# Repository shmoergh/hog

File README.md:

# Hog

Fully analog two-voice monophonic synth for live performances.

Details and user guide: [shmoergh.com](https://shmoergh.com/)

Latest revision: rev #3.

## Build

The HOG is a very fun but equally advanced electronics project. It's fully open source and we've put together a build guide for the brave ones who decide to build one. Let us know if you have questions and definitely share some pics of your builds (follow [Shmøergh on Instagram](https://www.instagram.com/shmoergh/)).

[Open build guide &rarr;](https://www.shmoergh.com/guides/hog-build-guide)

## BOMs

The HOG consists of 5 separate boards which you can find in the `boards` folder. Each board has it's own gerber files for JLCPCB PCB and Mouser BOMs in the board's `production` folders. The Core and Filter boards have SMD components too for which you can find JLCPCB assembly files (BOM and position) in the `production/jlcpcb` folder.

## Cloning

The MIDI2CV module uses [`pico-lib`](https://github.com/peterzimon/pico-lib) submodule. Make sure you clone
the repo like with its submodules:

```console
git clone --recurse-submodules git@github.com:shmoergh/hog.git
```

## License

Shmoergh Hog © 2024

Hardware is licensed under [CC BY-NC 4.0](https://creativecommons.org/licenses/by-nc/4.0/)

Software is licensed under [MIT](https://opensource.org/license/mit).

Font used on PCBs: <https://departuremono.com>

Simulations made in [CircuitJS](https://www.falstad.com/circuit/circuitjs.html)

## Disclaimer

All electronic projects and designs presented on this web site, or associated web sites should be considered dangerous if not lethal if not used safely. When working on projects based on the designs on this site, use extreme care to ensure that you do not come into contact with mains AC voltages or high voltage DC. If you are not confident about working with mains voltages, or high voltages, or you are not legally allowed to work with mains voltages, or high voltages, you are advised not to attempt work on them. The author, host, and all people associated with these web pages disclaim any liability for damages should anyone be killed or injured while working on these projects, or projects based on these designs, or any other project or design presented on these web pages and any associated web pages. The author, host, and all people associated with these web pages also disclaim any liability for projects, or projects based on these designs, or any other project or design presented on these web pages and any associated web pages when used in such a way as to infringe relevant government regulations and by-laws.

All circuits, schematics, printed circuit board, panel design and associated data published on this site can be used for private use only.

We are not responsible for any errors in the PCB design or the parts list. All responsibility for ordering PCBs, components, and assembly services rests solely with you.

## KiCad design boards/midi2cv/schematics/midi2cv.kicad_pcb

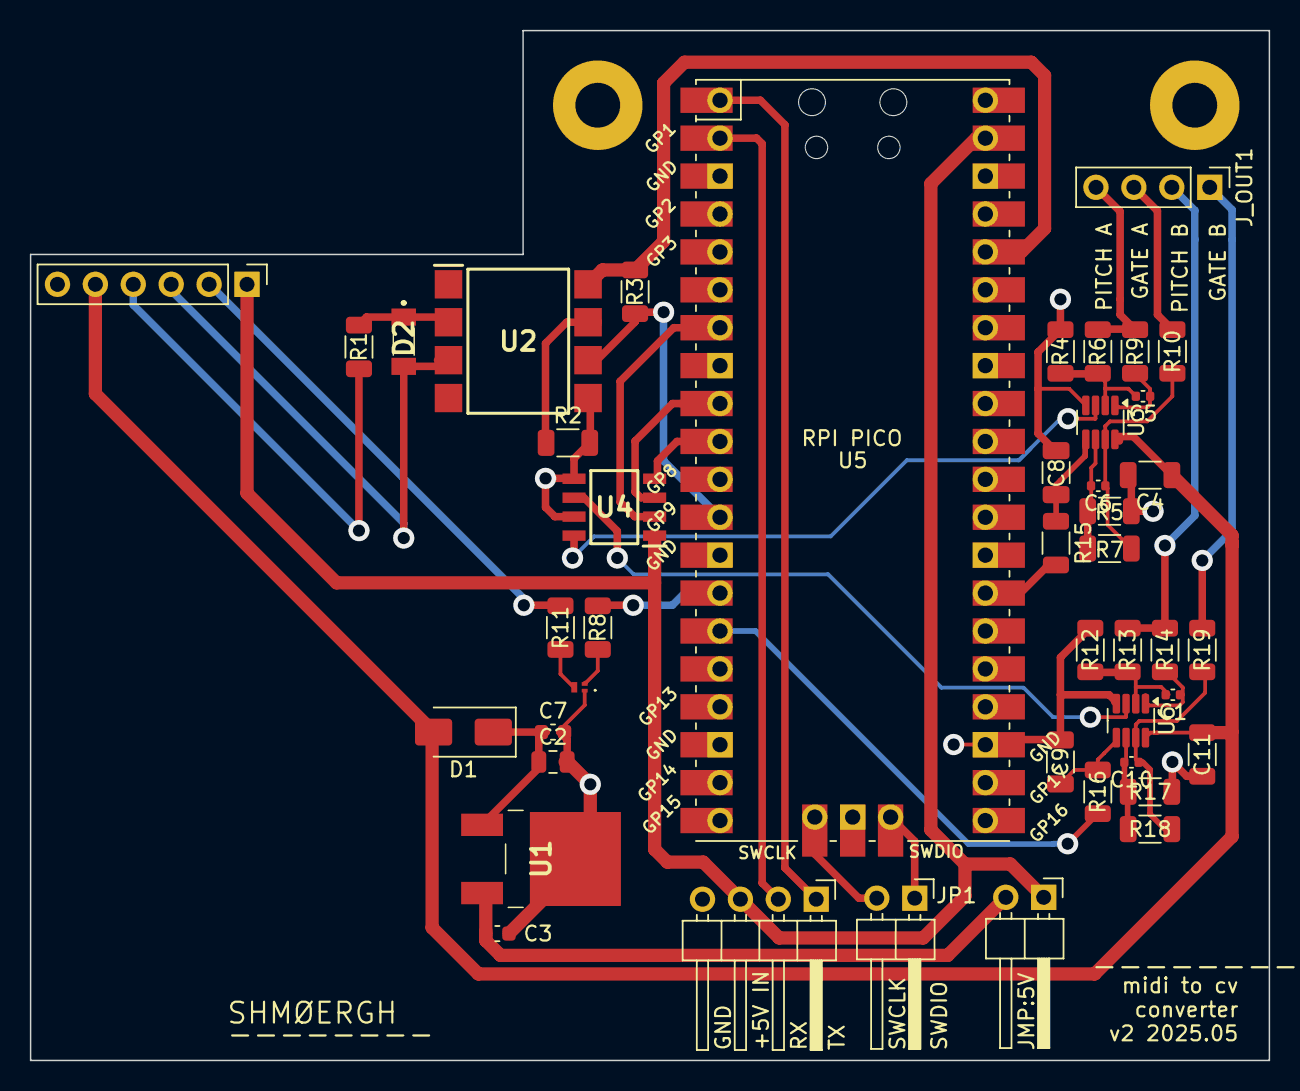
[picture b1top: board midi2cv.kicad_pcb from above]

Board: 2 copper layers, 83.0 x 69.0 mm, 46 parts (0 on the bottom side), 40 nets.

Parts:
C1, C5, C6, C10: 22p; C_0402_1005Metric
C2: 330n; C_0805_2012Metric
C3: 100n; C_0603_1608Metric
C4, C11: 100n; R_1206_3216Metric
C7: 10u; C_0603_1608Metric
C8, C9: 1u; C_1206_3216Metric
D1: S1A; D_SMA
D2: FDLL4148; FDLL4448
H1, H2: MountingHole; MountingHole_3mm_Pad
JP1: Jumper_2_Open; PinHeader_1x02_P2.54mm_Horizontal
J_IN1: Conn_01x06; PinHeader_1x06_P2.54mm_Vertical
J_OUT1: Conn_01x04; PinHeader_1x04_P2.54mm_Vertical
J_SWCLKDIO1: Conn_01x02; PinHeader_1x02_P2.54mm_Horizontal
J_SWD_IO1: Conn_01x04; PinHeader_1x04_P2.54mm_Horizontal
Q_GATE_LED1: MMBT3904LP-7; MMBT3904LP7
R1, R3: 220; R_1206_3216Metric
R2: 4.7k; R_1206_3216Metric
R4, R12: 47k; R_1206_3216Metric
R5, R17: 100k; R_1206_3216Metric
R6, R13: 68k; R_1206_3216Metric
R7, R18: 51k; R_1206_3216Metric
R8: 10k; R_1206_3216Metric
R9, R10, R14, R15, R16, R19: 1k; R_1206_3216Metric
R11: 470; R_1206_3216Metric
U1: L7805CDT-TR; L7805CDTTR
U2: 6N138S-TA1; SOP254P1030X508-8N
U3, U6: LM358; SOT-23-8
U4: MCP4822-E/SN; SOIC127P600X175-8N
U5: Pico; RPi_Pico_SMD_TH

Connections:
+3.3V: R3.1, U2.8 (VCC), U5.36 (3V3)
+5V: JP1.1 (A), J_IN1.1, J_SWD_IO1.3, U4.1 (Vdd), U5.39 (VSYS)
+12V: C4.1, C11.1, D1.2 (A), J_IN1.5, U3.8 (V+), U6.8 (V+)
DAC_A: U3.3 (+), U4.8 (VA)
DAC_B: U4.6 (VB), U6.3 (+)
DAC_CS: U4.2 (~CS), U5.7 (GPIO5)
DAC_SCK: U4.3 (SCK), U5.9 (GPIO6)
DAC_SDI: U4.4 (SDI), U5.10 (GPIO7)
GATE_A: J_OUT1.3, R10.1
GATE_A_TRIG: R15.2, U5.27 (GPIO21)
GATE_B: J_OUT1.1, R19.1
GATE_B_TRIG: R16.2, U5.15 (GPIO11)
GND: C2.2, C3.2, C4.2, C7.2, C8.2, C9.2, C11.2, J_IN1.6, J_SWD_IO1.4, Q_GATE_LED1.1 (E), R2.2, R4.2, R5.2, R12.2, R17.2, U1.2 (GND), U2.5 (GND), U3.4 (V-), U4.5 (~LDAC), U4.7 (Vss), U5.3 (GND), U5.8 (GND), U5.13 (GND), U5.18 (GND), U5.23 (GND), U5.28 (GND), U5.38 (GND), U6.4 (V-)
LED_GND: J_IN1.2, R11.1
LED_OUT: R8.1, U5.14 (GPIO10)
MIDI_4R: J_IN1.4, R1.2
MIDI_5T: D2.2 (A), J_IN1.3, U2.3 (C2)
MIDI_IN: R3.2, U2.6 (VO2), U5.12 (GPIO9)
unnamed: C1.1, R14.2, U6.1
unnamed: C5.1, R9.2, U3.1
unnamed: C6.1, R7.1, R10.2, U3.7
unnamed: C10.1, R18.1, R19.2, U6.7
unnamed: C2.1, C7.1, D1.1 (K), U1.1 (INPUT)
unnamed: D2.1 (K), R1.1, U2.2 (C1)
unnamed: C3.1, JP1.2 (B), U1.3 (OUTPUT)
unnamed: J_SWCLKDIO1.1, U5.43 (SWDIO)
unnamed: J_SWCLKDIO1.2, U5.41 (SWCLK)
unnamed: Q_GATE_LED1.2 (B), R8.2
unnamed: Q_GATE_LED1.3 (C), R11.2
unnamed: R2.1, U2.7 (VO1)
unnamed: C5.2, R4.1, R6.2, U3.2 (-)
unnamed: C8.1, R15.1, U3.5 (+)
unnamed: C6.2, R5.1, R7.2, U3.6 (-)
unnamed: C1.2, R12.1, R13.2, U6.2 (-)
unnamed: C9.1, R16.1, U6.5 (+)
unnamed: C10.2, R17.1, R18.2, U6.6 (-)
PITCH_A: J_OUT1.4, R6.1, R9.1
PITCH_B: J_OUT1.2, R13.1, R14.1
UART_RX: J_SWD_IO1.2, U5.2 (GPIO1)
UART_TX: J_SWD_IO1.1, U5.1 (GPIO0)

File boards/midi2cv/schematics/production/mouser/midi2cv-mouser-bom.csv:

"Reference","Value","Datasheet","Footprint","Quantity 1","DNP","Mouser Part Number","Part URL","Vendor"
"C1,C5,C6,C10","22p","~","-- mixed values --","4",,"594-K220J15C0GF53L2 ","https://mou.sr/3ZTXYXB","Mouser"
"C2","330n","~","Capacitor_THT:C_Disc_D3.0mm_W2.0mm_P2.50mm","1",,"810-FA14X7R1H334KNU6 ","https://mou.sr/4gDlMo9","Mouser"
"C3,C4,C11","100n","~","Capacitor_THT:C_Disc_D3.0mm_W2.0mm_P2.50mm","3",,"594-K103K15X7RF5TK2 ","https://mou.sr/3VFZIRH","Mouser"
"C7","10u","~","Capacitor_THT:CP_Radial_D6.3mm_P2.50mm","1",,"80-ESS106M035AC2EA ","https://mou.sr/49DyMaU","Mouser"
"C8,C9","1u","~","Capacitor_THT:CP_Radial_D6.3mm_P2.50mm","2",,"140-SG1R0M1H0407P ","https://mou.sr/41BqE8O","Mouser"
"D1","1N4001","~","Diode_THT:D_DO-41_SOD81_P10.16mm_Horizontal","1",,"637-1N4001 ","https://mou.sr/3DfEJyK","Mouser"
"D2","1N4148","~","Diode_THT:D_DO-35_SOD27_P7.62mm_Horizontal","1",,"512-1N4148 ","https://mou.sr/3ZP7Wt3","Mouser"
"JP1","Jumper_2_Open","~","Connector_PinHeader_2.54mm:PinHeader_1x02_P2.54mm_Horizontal","1",,"737-PH1RB-02-UA ","https://mou.sr/3D93YT9","Mouser"
"J_IN1","Conn_01x06","~","Connector_PinHeader_2.54mm:PinHeader_1x06_P2.54mm_Vertical","1",,"737-RS1-06-G ","https://mou.sr/3BuZUME","Mouser"
"J_OUT1,J_SWD_IO1","Conn_01x04","~","-- mixed values --","2",,"737-RS1-04-G ","https://mou.sr/4gDjs0p","Mouser"
"J_SWCLKDIO1","Conn_01x02","~","Connector_PinHeader_2.54mm:PinHeader_1x02_P2.54mm_Horizontal","1",,"737-PH1RB-02-UA ","https://mou.sr/3D93YT9","Mouser"
"Q_GATE_LED1","2N3904","https://www.onsemi.com/pub/Collateral/2N3903-D.PDF","Package_TO_SOT_THT:TO-92_Inline_Wide","1",,"637-2N3904 ","https://mou.sr/4febysZ","Mouser"
"R1,R3","220","~","Shmoergh_Custom_Footprints:R_Axial_DIN0207_L6.3mm_D2.5mm_P7.62mm_Horizontal","2",,"303-MF0W4FF2200B00 ","https://mou.sr/4iu83Sh","Mouser"
"R2","4.7k","~","Shmoergh_Custom_Footprints:R_Axial_DIN0207_L6.3mm_D2.5mm_P7.62mm_Horizontal","1",,"303-MF0W4FF4701A10 ","https://mou.sr/41yABnC","Mouser"
"R4,R12","47k","~","Shmoergh_Custom_Footprints:R_Axial_DIN0207_L6.3mm_D2.5mm_P7.62mm_Horizontal","2",,"303-CFR0W4J0473B00 ","https://mou.sr/3VFb8Fd","Mouser"
"R5,R17","100k","~","Shmoergh_Custom_Footprints:R_Axial_DIN0207_L6.3mm_D2.5mm_P7.62mm_Horizontal","2",,"303-MF0W4FF1003T50 ","https://mou.sr/3BGpE8K","Mouser"
"R6,R13","68k","~","Shmoergh_Custom_Footprints:R_Axial_DIN0207_L6.3mm_D2.5mm_P7.62mm_Horizontal","2",,"603-MFR-25FBF52-68K ","https://mou.sr/4gyTECt","Mouser"
"R7,R18","51k","~","Shmoergh_Custom_Footprints:R_Axial_DIN0207_L6.3mm_D2.5mm_P7.62mm_Horizontal","2",,"303-MF0W4FF5102B00 ","https://mou.sr/3OXlwVc","Mouser"
"R8","10k","~","Shmoergh_Custom_Footprints:R_Axial_DIN0207_L6.3mm_D2.5mm_P7.62mm_Horizontal","1",,"303-MF0W4FF1002T50 ","https://mou.sr/4gfXSiu","Mouser"
"R9,R10,R14,R15,R16,R19","1k","~","Shmoergh_Custom_Footprints:R_Axial_DIN0207_L6.3mm_D2.5mm_P7.62mm_Horizontal","6",,"303-MF0W4FF1001A10 ","https://mou.sr/3De3mMa","Mouser"
"R11","470","~","Shmoergh_Custom_Footprints:R_Axial_DIN0207_L6.3mm_D2.5mm_P7.62mm_Horizontal","1",,"303-MF0W4FF4700A10 ","https://mou.sr/3DjrzRq","Mouser"
"U1","LM7805_TO220","https://www.onsemi.cn/PowerSolutions/document/MC7800-D.PDF","Package_TO_SOT_THT:TO-220-3_Horizontal_TabDown","1",,"926-LM7805CT/NOPB ","https://mou.sr/4gwivXu","Mouser"
"U2","6N138","http://www.onsemi.com/pub/Collateral/HCPL2731-D.pdf","Package_DIP:DIP-8_W7.62mm_LongPads","1",,"859-6N138M ","https://mou.sr/3VDrRsD","Mouser"
"U3,U6","LM358","http://www.ti.com/lit/ds/symlink/lm2904-n.pdf","Package_DIP:DIP-8_W7.62mm_LongPads","2",,"595-LM358P ","https://mou.sr/4izjQPc","Mouser"
"U4","MCP4822","http://ww1.microchip.com/downloads/en/DeviceDoc/20002249B.pdf","Package_DIP:DIP-8_W7.62mm_LongPads","1",,"579-MCP4822-E/P ","https://mou.sr/4gecDm5","Mouser"
"U5","Pico",,"MCU_RaspberryPi_and_Boards:RPi_Pico_SMD_TH","1",,"358-SC0915 ","https://mou.sr/49BoTdS","Mouser"

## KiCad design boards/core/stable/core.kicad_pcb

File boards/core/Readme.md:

## Core board

Circuit for all core modules of HOG:

- 2x VCO
- 2x Waveshapers
- VCA
- ADSR
- 2x LFO
- Sub source
- Noise source
- Output

### Versions

**Experimental** — Some parts of the circuit contains multiple solutions, options that can be selected to build. In this version there are multiple ways to build thermal compensation for the VCOs depending on component availability (NTC based, PTS100 based); it contains a precision +/-5V circuit with output connectors that can be used on the UI board if necessary; and misc. options.

**Stable** — This is the opinionated, tested and recommended version of the core board. Compared to the experimental board:

- This board uses PTS100 for thermal compensation
- It is designed for SMD manufacturing. Note that some parts are not available at JLCPCB. We kept these THT whereever it's possible for easy build.
- +/-5V precision output is removed. Instead +/-12V resistor divider is used where needed, as approximate values were fine on the Core board.

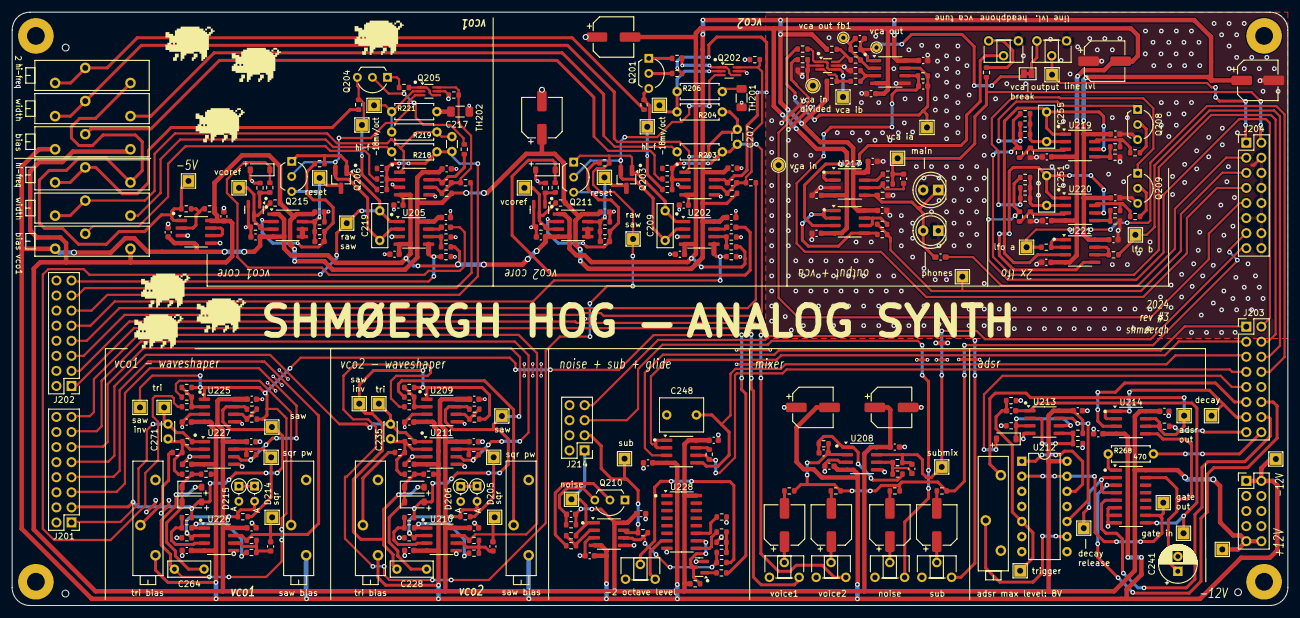
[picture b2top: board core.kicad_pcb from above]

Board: 2 copper layers, 215.0 x 100.0 mm, 351 parts (0 on the bottom side), 186 nets.

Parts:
C201, C202, C203, C204, C205, C206, C211, C212, C213, C214, C215, C216, C221, C222, C223, C224, C229, C230, C231, C232, C233, C234, C237, C238, C239, C242, C243, C244, C245, C246, C247, C249, C250, C253, C254, C257, C258, C259, C262, C263, C265, C266, C267, C268, C269, C270, C278, C279: 100n; C_0603_1608Metric
C207, C217: 100p-1n; C_Disc_D3.0mm_W1.6mm_P2.50mm
C208, C218, C276: 100p; C_0603_1608Metric
C209, C219: 2.2nF (foil); C_Rect_L7.2mm_W2.5mm_P5.00mm_FKS2_FKP2_MKS2_MKP2
C210, C220: 22p; C_0603_1608Metric
C225, C226, C227, C275: 22uF; CP_Elec_6.3x5.4
C228, C264: 10p-100p; C_Rect_L7.0mm_W2.5mm_P5.00mm
C235, C271: 22p; C_Disc_D3.0mm_W2.0mm_P2.50mm
C236, C272: 33p; C_0603_1608Metric
C240: 10n; C_0603_1608Metric
C241: 10u; CP_Radial_D6.3mm_P2.50mm
C248: 1u (foil or electrolite); C_Rect_L7.2mm_W5.5mm_P5.00mm_FKS2_FKP2_MKS2_MKP2
C251, C255: 22n-47n (foil); C_Rect_L7.0mm_W2.5mm_P5.00mm
C252, C256, C280, C281: 47u; CP_Elec_6.3x5.4
C260, C261: 100u; CP_Elec_6.3x7.7
C273, C274, C282, C283, C284, C285: 47p; C_0603_1608Metric
C277: 1u; C_0603_1608Metric_Pad1.08x0.95mm_HandSolder
D203, D204, D207, D212, D213, D216, D217: 1N4148; D_SOD-123
D205, D206, D214, D215: 5.1V; D_DO-34_SOD68_P2.54mm_Vertical_AnodeUp
D_NEGATIVE_LIMITER201: Red LED; LED_D5.0mm
D_POSITIVE_LIMITER201: Red LED; LED_D5.0mm
H201, H202, H203, H204: MountingHole; MountingHole_3mm_Pad
J201, J202, J203, J204: Conn_02x08_Counter_Clockwise; PinHeader_2x08_P2.54mm_Vertical
J214: Conn_02x04_Counter_Clockwise; PinHeader_2x04_P2.54mm_Vertical
JP202: Breakpoint; SolderJumper-2_P1.3mm_Bridged_Pad1.0x1.5mm
J_POWER201: Conn_02x05_Odd_Even; PinHeader_2x05_P2.54mm_Vertical
Q201, Q204: 2N3906; TO-92L_Inline_Wide
Q202, Q205, Q207: BC847BS; SOT-363_SC-70-6_Handsoldering
Q203, Q206: MMBFJ111; SOT-23_Handsoldering
Q208, Q209, Q210: BC548C; TO-92L_Inline_Wide
Q211, Q215: J111; TO-92_Inline_Wide
Q212, Q213, Q214: MMBT5551; SOT-23
R201, R213, R216, R228, R232, R235, R237, R242, R243, R244, R246, R247, R250, R252, R253, R254, R255, R262, R263, R264, R278, R279, R280, R281, R282, R283, R284, R285, R286, R287, R301, R304, R306, R307, R308, R309, R316, R317, R318, R319, R326, R327, R328, R329, R335, R336, R337, R338, R339, R340: 100k; R_0603_1608Metric
R202, R212, R217, R227: 150k; R_0603_1608Metric
R203, R218: 91k; R_Axial_DIN0207_L6.3mm_D2.5mm_P7.62mm_Horizontal
R204, R219: 6.2k (50ppm); R_Axial_DIN0207_L6.3mm_D2.5mm_P7.62mm_Horizontal
R205, R208, R220, R223, R322, R323: 1M; R_0603_1608Metric
R206, R221: 4R22 (50ppm); R_Axial_DIN0207_L6.3mm_D2.5mm_P7.62mm_Horizontal
R207, R209, R222, R224: 1.5k; R_0603_1608Metric
R210, R225: 510; R_0603_1608Metric
R211, R226: 22k; R_0603_1608Metric
R214, R229: 330k; R_0603_1608Metric
R215, R230, R258, R297, R312: 2.2k; R_0603_1608Metric
R231: 4.7k; R_0603_1608Metric
R233: 220; R_0603_1608Metric
R234, R245: 33k; R_0603_1608Metric
R236, R238, R239, R266, R288, R289, R324, R325: 10k; R_0603_1608Metric
R240, R241, R296: 470k; R_0603_1608Metric
R248, R249, R302, R303: 15k; R_0603_1608Metric
R251, R305: 27k; R_0603_1608Metric
R256, R259, R310, R313, R320: 220k; R_0603_1608Metric
R257, R267, R290, R291, R292, R293, R311, R321, R330, R331, R332, R333, R334: 47k; R_0603_1608Metric
R260, R314: 2.2M; R_0603_1608Metric
R261, R300, R315: 240k; R_0603_1608Metric
R265: 75k; R_0603_1608Metric
R268: 470; R_Axial_DIN0207_L6.3mm_D2.5mm_P7.62mm_Horizontal
R269, R272, R277, R294, R295: 1k; R_0603_1608Metric
R270: 100k; R_0603_1608Metric_Pad0.98x0.95mm_HandSolder
R271: 150; R_0603_1608Metric
R273, R274: 100; R_0603_1608Metric
R298: 3.3M; R_0603_1608Metric
RV201, RV202, RV203, RV204, RV205: 100k; Potentiometer_ACP_CA6-H2,5_Horizontal
RV_ADSR_MAX_VOLTAGE201: 100k; Potentiometer_Bourns_3006P_Horizontal
RV_HEADPHONE_LIM201: 100k; Potentiometer_ACP_CA6-H2,5_Horizontal
RV_LINE_OUT_LVL201: 10k; Potentiometer_ACP_CA6-H2,5_Horizontal
RV_SAW_BIAS201, RV_SAW_BIAS202: 10k; Potentiometer_Bourns_3006P_Horizontal
RV_TRI_BIAS201, RV_TRI_BIAS202: 100k; Potentiometer_Bourns_3006P_Horizontal
R_BIAS201, R_BIAS203: 100k (prec); Potentiometer_Bourns_3006P_Horizontal
R_HIFREQ201, R_HIFREQ202: 2k (prec); Potentiometer_Bourns_3006P_Horizontal
R_WIDTH201, R_WIDTH202: 20k; Potentiometer_Bourns_3006P_Horizontal
TH201, TH202: PTS120601B100RP100; R_1206_3216Metric_Pad1.30x1.75mm_HandSolder
TP201, TP205: -18mV/V; TestPoint_THTPad_2.0x2.0mm_Drill1.0mm
TP202, TP206: HiFreq; TestPoint_THTPad_2.0x2.0mm_Drill1.0mm
TP203, TP207: VCOVREF; TestPoint_THTPad_2.0x2.0mm_Drill1.0mm
TP204, TP208: Reset OUT; TestPoint_THTPad_2.0x2.0mm_Drill1.0mm
TP209, TP210: SAWInv; TestPoint_THTPad_2.0x2.0mm_Drill1.0mm
TP211, TP212: SAW; TestPoint_THTPad_2.0x2.0mm_Drill1.0mm
TP213, TP214: TRI; TestPoint_THTPad_2.0x2.0mm_Drill1.0mm
TP215, TP216: PW; TestPoint_THTPad_2.0x2.0mm_Drill1.0mm
TP217, TP218: SQR; TestPoint_THTPad_2.0x2.0mm_Drill1.0mm
TP219: NOISE; TestPoint_THTPad_2.0x2.0mm_Drill1.0mm
TP220: DR_OUT; TestPoint_THTPad_2.0x2.0mm_Drill1.0mm
TP221: TRIG; TestPoint_THTPad_2.0x2.0mm_Drill1.0mm
TP222: Gate2; TestPoint_THTPad_2.0x2.0mm_Drill1.0mm
TP223: Gate1; TestPoint_THTPad_2.0x2.0mm_Drill1.0mm
TP224: Submix; TestPoint_THTPad_2.0x2.0mm_Drill1.0mm
TP225: IVCA_A; TestPoint_THTPad_2.0x2.0mm_Drill1.0mm
TP226: IVCA_B; TestPoint_THTPad_2.0x2.0mm_Drill1.0mm
TP227: MAINOUT; TestPoint_THTPad_2.0x2.0mm_Drill1.0mm
TP228: MAX_LINEOUT; TestPoint_THTPad_2.0x2.0mm_Drill1.0mm
TP229: PHONES_OUT; TestPoint_THTPad_2.0x2.0mm_Drill1.0mm
TP230: LFO_A_OUT; TestPoint_THTPad_2.0x2.0mm_Drill1.0mm
TP231: LFO_B_OUT; TestPoint_THTPad_2.0x2.0mm_Drill1.0mm
TP232: SUB; TestPoint_THTPad_2.0x2.0mm_Drill1.0mm
TP233, TP234: RAW_SAW; TestPoint_THTPad_2.0x2.0mm_Drill1.0mm
TP235: 12V; TestPoint_THTPad_2.0x2.0mm_Drill1.0mm
TP236: -12V; TestPoint_THTPad_2.0x2.0mm_Drill1.0mm
TP237: -5V; TestPoint_THTPad_2.0x2.0mm_Drill1.0mm
TP_ADSR_OUT201: TestPoint; TestPoint_THTPad_2.0x2.0mm_Drill1.0mm
TP_SUSTAIN201: Sustain; TestPoint_THTPad_2.0x2.0mm_Drill1.0mm
TP_VCA_AU_IN201: VCA_IN_DIV; TestPoint_THTPad_D2.0mm_Drill1.0mm
TP_VCA_AU_IN202: VCA_IN; TestPoint_THTPad_D2.0mm_Drill1.0mm
TP_VCA_OUT201: VCA_OUT; TestPoint_THTPad_D1.5mm_Drill0.7mm
TP_VCA_OUT202: VCA_OUT_FB; TestPoint_THTPad_D1.5mm_Drill0.7mm
U201, U202, U204, U205, U207, U208, U209, U210, U211, U214, U217, U218, U219, U220, U221, U222, U223, U225, U226, U227: TL072; SOIC-8_3.9x4.9mm_P1.27mm
U203, U206: LM311; SOIC-8_3.9x4.9mm_P1.27mm
U212: 4002; DIP-14_W7.62mm
U213: LM358; SOIC-8_3.9x4.9mm_P1.27mm
U215: CD4053B; SOIC-16_3.9x9.9mm_P1.27mm
U216: NE5532; SOIC-8_3.9x4.9mm_P1.27mm
U228: CD4040BM96; SOIC-16_3.9x9.9mm_P1.27mm

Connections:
+12V: C201.1, C203.1, C205.1, C211.1, C213.1, C215.1, C221.1, C223.1, C229.1, C231.1, C233.1, C237.1, C238.1, C242.1, C244.1, C246.1, C249.1, C252.1, C253.1, C257.1, C258.1, C260.1, C262.1, C265.1, C267.1, C269.1, C278.1, C280.1, J_POWER201.9, J_POWER201.10, R208.1, R212.2, R223.1, R227.2, R235.2, R237.2, R265.1, R296.1, R300.1, R321.1, R_BIAS201.1, R_BIAS203.1, TP235.1, U201.8 (V+), U202.8 (V+), U203.8 (V+), U204.8 (V+), U205.8 (V+), U206.8 (V+), U207.8 (V+), U208.8 (V+), U209.8 (V+), U210.8 (V+), U211.8 (V+), U212.14 (VDD), U213.8 (V+), U214.8 (V+), U215.16 (VDD), U216.8 (V+), U217.8 (V+), U218.8 (V+), U219.8 (V+), U220.8 (V+), U221.8 (V+), U222.8 (V+), U223.8 (V+), U225.8 (V+), U226.8 (V+), U227.8 (V+), U228.16 (VDD)
-5V: R301.2, R_HIFREQ201.1, R_HIFREQ202.1, TP237.1, U223.1
-12V: C202.2, C204.2, C206.2, C212.2, C214.2, C216.2, C222.2, C224.2, C230.2, C232.2, C234.2, C239.2, C243.2, C245.2, C247.2, C250.2, C254.2, C256.2, C259.2, C261.2, C263.2, C266.2, C268.2, C270.2, C279.2, C281.2, J_POWER201.1, J_POWER201.2, R250.2, R304.2, R326.2, R327.2, RV_SAW_BIAS201.3, RV_SAW_BIAS202.3, RV_TRI_BIAS201.3, RV_TRI_BIAS202.3, R_BIAS201.3, R_BIAS203.3, TP236.1, U201.4 (V-), U202.4 (V-), U203.1 (GND), U203.4 (V-), U204.4 (V-), U205.4 (V-), U206.1 (GND), U206.4 (V-), U207.4 (V-), U208.4 (V-), U209.4 (V-), U210.4 (V-), U211.4 (V-), U214.4 (V-), U216.4 (V-), U217.4 (V-), U218.4 (V-), U219.4 (V-), U220.4 (V-), U221.4 (V-), U222.4 (V-), U223.4 (V-), U225.4 (V-), U226.4 (V-), U227.4 (V-)
/Buffers/LFO_A_IN: C255.1, U219.1, U219.6 (-), U221.3 (+)
/Buffers/LFO_B_IN: C251.1, U220.1, U220.6 (-), U221.5 (+)
/Output/AUDIO_IN: JP202.1 (A), RV_LINE_OUT_LVL201.3
/VCA/VCA_AUDIO_OUT: C285.2, JP202.2 (B), R241.2, TP_VCA_OUT201.1, U207.1
/VCO1 Waveshapers/SAW_INV: C264.2, D213.2 (A), R305.1, R308.2, R320.2, TP210.1, U225.1
/VCO2 Waveshapers/SAW_INV: C228.2, D204.2 (A), R251.1, R254.2, TP209.1, U209.1
/VCO 2/HI_FREQ_COMP: Q201.3 (C), R202.2, R210.1, TP202.1
/VCO 2/I_REF: C208.1, Q202.6 (C1), R205.2, R208.2, R339.2, U201.6 (-)
/VCO 2/RAW_SAW: C209.2, Q203.1 (D), Q211.1 (D), R211.1, R248.2, TP233.1, U202.1
/VCO/HI_FREQ_COMP: Q204.3 (C), R217.2, R225.1, TP206.1
/VCO/I_REF: C218.1, Q205.6 (C1), R220.2, R223.2, R340.2, U204.6 (-)
/VCO/RAW_SAW: C219.2, Q206.1 (D), Q215.1 (D), R226.1, R302.2, TP234.1, U205.1
ADSR_ENV_CV: J203.15, R269.1
ATTACK: J203.16, R268.2
DECAY: J203.12, U215.3 (C1)
DECAY_MAX: J203.13, TP_SUSTAIN201.1, U214.1, U214.2 (-)
EXTERNAL_INPUT: C282.1, J204.13, R242.2, R243.2, R244.2, R245.1, R338.2, U208.2 (-)
GLIDED_PITCH: J203.7, R277.1, U218.6 (-)
GLIDE_AMOUNT: C248.1, J203.5, U218.5 (+)
GND: C201.2, C202.1, C203.2, C204.1, C205.2, C206.1, C211.2, C212.1, C213.2, C214.1, C215.2, C216.1, C221.2, C222.1, C223.2, C224.1, C229.2, C230.1, C231.2, C232.1, C233.2, C234.1, C237.2, C238.2, C239.1, C241.2, C242.2, C243.1, C244.2, C245.1, C246.2, C247.1, C248.2, C249.2, C250.1, C252.2, C253.2, C254.1, C256.1, C258.2, C259.1, C260.2, C261.1, C262.2, C263.1, C265.2, C266.1, C267.2, C268.1, C269.2, C270.1, C278.2, C279.1, C280.2, C281.1, D206.2 (A), D215.2 (A), D216.2 (A), D217.2 (A), D_NEGATIVE_LIMITER201.2 (A), D_POSITIVE_LIMITER201.1 (K), J201.2, J201.4, J201.6, J201.8, J201.10, J201.12, J201.14, J201.16, J202.2, J202.4, J202.6, J202.8, J202.10, J202.12, J202.14, J202.16, J204.4, J204.6, J204.8, J204.10, J204.11, J204.12, J204.14, J204.16, J214.2, J214.4, J214.6, J214.8, J_POWER201.3, J_POWER201.4, J_POWER201.5, J_POWER201.6, J_POWER201.7, J_POWER201.8, Q202.5 (B2), Q205.5 (B2), Q207.5 (B2), Q208.3 (E), Q209.3 (E), Q212.2 (E), Q213.2 (E), Q214.2 (E), R213.1, R215.2, R228.1, R230.2, R233.2, R240.1, R259.2, R264.1, R266.2, R267.2, R270.1, R286.2, R287.2, R290.2, R291.2, R313.2, R322.2, R323.2, R324.1, R325.1, R330.2, R331.2, R332.2, R334.1, R339.1, R340.1, RV201.1, RV202.1, RV203.1, RV204.1, RV205.1, RV_ADSR_MAX_VOLTAGE201.3, RV_HEADPHONE_LIM201.1, RV_LINE_OUT_LVL201.1, RV_SAW_BIAS201.1, RV_SAW_BIAS202.1, RV_TRI_BIAS201.1, RV_TRI_BIAS202.1, TH201.2, TH202.2, U201.3 (+), U201.5 (+), U202.3 (+), U204.3 (+), U204.5 (+), U205.3 (+), U207.5 (+), U208.3 (+), U208.5 (+), U209.3 (+), U209.5 (+), U210.5 (+), U211.3 (+), U211.5 (+), U212.3, U212.4, U212.7 (VSS), U212.11, U213.4 (V-), U215.6 (INH), U215.7 (VEE), U215.8 (VSS), U217.3 (+), U222.3 (+), U222.5 (+), U223.3 (+), U223.5 (+), U225.3 (+), U225.5 (+), U226.5 (+), U227.3 (+), U227.5 (+), U228.8 (VSS)
HEADPHONES: J204.5, R273.1, R274.1, TP229.1
KB_GATE: D207.2 (A), J203.9
KB_PITCH: J203.1, U218.3 (+)
LFO_A: J203.8, R294.1, TP230.1
LFO_A_RATE: J203.4, R278.1, R279.2
LFO_B: J203.6, R295.1, TP231.1
LFO_B_RATE: J203.2, R280.1, R281.2
MAIN_OUT: C276.2, J204.2, R231.1, R271.1, R272.2, TP227.1
MAIN_VOL_IN: C277.1, J204.3
MAIN_VOL_MAX: J204.1, RV_LINE_OUT_LVL201.2, TP228.1
NOISE: J214.1, R298.2, TP219.1, U222.1
NOISE_AUDIO: J214.5, RV202.3
unnamed: C207.2, R204.1, R_WIDTH201.2, R_WIDTH201.3, U201.1
unnamed: C208.2, R207.1, U201.7
unnamed: C217.2, R219.1, R_WIDTH202.2, R_WIDTH202.3, U204.1
unnamed: C218.2, R222.1, U204.7
unnamed: C225.1, RV201.2
unnamed: C225.2, R242.1
unnamed: C226.1, RV205.2
unnamed: C226.2, R243.1
unnamed: C227.1, RV202.2
unnamed: C227.2, R244.1
unnamed: C240.1, R267.1, TP221.1, U212.5
unnamed: C273.1, U202.7
unnamed: C274.1, U205.7
unnamed: C275.1, RV204.2
unnamed: C275.2, R338.1
unnamed: C282.2, R245.2, R246.1, U208.1
unnamed: C284.2, R234.2, R236.1, TP226.1, U207.7
unnamed: C228.1, D203.1 (K), D204.1 (K), R250.1, R252.2
unnamed: D205.2 (A), R257.1, R259.1, U210.2 (-)
unnamed: D205.1 (K), D206.1 (K)
unnamed: D207.1 (K), R264.2, U213.3 (+), U213.6 (-)
unnamed: C264.1, D212.1 (K), D213.1 (K), R304.1, R306.2
unnamed: D214.2 (A), R311.1, R313.1, U226.2 (-)
unnamed: D214.1 (K), D215.1 (K)
unnamed: C273.2, D216.1 (K), R328.1
unnamed: C274.2, D217.1 (K), R329.1
unnamed: C277.2, D_NEGATIVE_LIMITER201.1 (K), D_POSITIVE_LIMITER201.2 (A), R270.2, U217.5 (+)
unnamed: Q201.2 (B), R207.2
unnamed: Q201.1 (E), R209.2
unnamed: Q202.2 (B1), R204.2, R206.1, TP201.1
unnamed: C209.1, Q202.3 (C2), Q203.2 (S), Q211.2 (S), U202.2 (-)
unnamed: Q202.1 (E1), Q202.4 (E2), R209.1
unnamed: C210.2, Q203.3 (G), Q211.3 (G), R214.2, R215.1, TP204.1, U203.7
unnamed: Q204.2 (B), R222.2
unnamed: Q204.1 (E), R224.2
unnamed: Q205.2 (B1), R219.2, R221.1, TP205.1
unnamed: C219.1, Q205.3 (C2), Q206.2 (S), Q215.2 (S), U205.2 (-)
unnamed: Q205.1 (E1), Q205.4 (E2), R224.1
unnamed: C220.2, Q206.3 (G), Q215.3 (G), R229.2, R230.1, TP208.1, U206.7
unnamed: Q207.2 (B1), R232.2, R233.1, TP_VCA_AU_IN201.1
unnamed: Q207.6 (C1), R235.1, R238.1
unnamed: Q207.3 (C2), R237.1, R239.1
unnamed: Q207.1 (E1), Q207.4 (E2), R236.2, TP225.1
unnamed: Q208.2 (B), R288.2
unnamed: Q208.1 (C), R282.1, R284.2
unnamed: Q209.2 (B), R289.2
unnamed: Q209.1 (C), R283.1, R285.2
unnamed: Q210.2 (B), R297.1
unnamed: C257.2, Q210.3 (E), R296.2
unnamed: Q212.1 (B), R320.1
unnamed: Q212.3 (C), R321.2, U228.10 (CLK)
unnamed: Q213.1 (B), R328.2, R330.1
unnamed: Q213.3 (C), R212.1, R213.2, TP203.1, U203.3 (-)
unnamed: Q214.1 (B), R329.2, R331.1
unnamed: Q214.3 (C), R227.1, R228.2, TP207.1, U206.3 (-)
unnamed: R203.2, R_WIDTH201.1
unnamed: R206.2, TH201.1
unnamed: R210.2, R_HIFREQ201.2, R_HIFREQ201.3
unnamed: R218.2, R_WIDTH202.1
unnamed: R221.2, TH202.1
unnamed: R225.2, R_HIFREQ202.2, R_HIFREQ202.3
unnamed: R249.2, RV_SAW_BIAS201.2
unnamed: R253.2, RV_TRI_BIAS201.2
unnamed: R257.2, R262.2, TP215.1, U211.7
unnamed: R260.1, R261.2, U210.1
unnamed: R271.2, U217.7
unnamed: R272.1, RV_HEADPHONE_LIM201.3
unnamed: R277.2, U218.7
unnamed: R288.1, R292.2, U219.7
unnamed: R289.1, R293.2, U220.7
unnamed: R303.2, RV_SAW_BIAS202.2
unnamed: R307.2, RV_TRI_BIAS202.2
unnamed: R311.2, R316.2, TP216.1, U227.7
unnamed: R314.1, R315.2, U226.1
unnamed: R318.1, R_BIAS203.2
unnamed: R319.1, R_BIAS201.2
unnamed: R333.1, R334.2, R335.2
unnamed: R336.2, RV203.2
unnamed: RV_ADSR_MAX_VOLTAGE201.2, U212.9
unnamed: R324.2, R326.1, U202.6 (-)
unnamed: C210.1, R211.2, R214.1, U203.2 (+)
unnamed: U203.5 (BAL), U203.6 (STRB)
unnamed: R325.2, R327.1, U205.6 (-)
unnamed: C220.1, R226.2, R229.1, U206.2 (+)
unnamed: U206.5 (BAL), U206.6 (STRB)
unnamed: R239.2, R240.2, U207.3 (+)
unnamed: C285.1, R238.2, R241.1, TP_VCA_OUT202.1, U207.2 (-)
unnamed: C283.1, R246.2, R247.1, U208.6 (-)
unnamed: R248.1, R249.1, R251.2, U209.2 (-)
unnamed: R254.1, R255.2, U209.6 (-)
unnamed: R258.1, R260.2, U210.3 (+)
unnamed: C236.1, R261.1, R263.2, U210.6 (-)
unnamed: C235.2, R252.1, R253.1, R256.2, U211.2 (-)
unnamed: U212.1, U212.12
unnamed: U212.10, U213.7
unnamed: R265.2, R266.1, U213.2 (-), U213.5 (+)
unnamed: C241.1, U214.5 (+), U215.15 (B)
unnamed: R269.2, RV_ADSR_MAX_VOLTAGE201.1, TP_ADSR_OUT201.1, U214.6 (-), U214.7
unnamed: TP220.1, U215.2 (B0), U215.4 (C)
unnamed: R268.1, U215.1 (B1)
unnamed: TP222.1, U212.2, U212.13, U215.10 (S2)
unnamed: C240.2, TP223.1, U213.1, U215.9 (S3)
unnamed: RV_HEADPHONE_LIM201.2, U216.3 (+)
unnamed: R274.2, U216.1, U216.2 (-), U216.5 (+)
unnamed: R273.2, U216.6 (-), U216.7
unnamed: U217.1, U217.2 (-)
unnamed: C276.1, R231.2, U217.6 (-)
unnamed: R279.1, R286.1, U219.3 (+)
unnamed: C255.2, R278.2, R282.2, R284.1, U219.2 (-)
unnamed: R290.1, R292.1, U219.5 (+)
unnamed: R281.1, R287.1, U220.3 (+)
unnamed: C251.2, R280.2, R283.2, R285.1, U220.2 (-)
unnamed: R291.1, R293.1, U220.5 (+)
unnamed: R294.2, U221.1, U221.2 (-)
unnamed: R295.2, U221.6 (-), U221.7
unnamed: R297.2, R298.1, U222.2 (-)
unnamed: R335.1, R336.1, R337.2, U222.6 (-)
unnamed: R300.2, R301.1, U223.2 (-)
unnamed: U223.6 (-), U223.7
unnamed: R302.1, R303.1, R305.2, U225.2 (-)
unnamed: R308.1, R309.2, U225.6 (-)
unnamed: R312.1, R314.2, U226.3 (+)
unnamed: C272.1, R315.1, R317.2, U226.6 (-)
unnamed: C271.2, R306.1, R307.1, R310.2, U227.2 (-)
unnamed: R333.2, U228.9 (Q0)
unnamed: RV203.3, U228.7 (Q1)
unnamed: R332.1, U228.11 (Reset)
PITCH_BUFFERED: J203.3, U218.1, U218.2 (-)
RELEASE: J203.14, U215.5 (C0)
SUB: J214.3, R337.1, TP232.1, U222.7
SUBMIX: C283.2, J204.15, R247.2, TP224.1, U208.7
SUB_AUDIO: J214.7, RV204.3
SUSTAIN: J203.11, U214.3 (+)
VCA_AUDIO_IN: J204.9, R232.1, TP_VCA_AU_IN202.1
VCA_ENV_CV: C284.1, J204.7, R234.1, U207.6 (-)
VCO1_AUDIO: J202.1, RV201.3
VCO1_CV: C217.1, J202.11, R216.2, R217.1, R218.1, R319.2, U204.2 (-)
VCO1_FM: J202.13, R220.1
VCO1_SAW: D212.2 (A), J201.3, R309.1, R312.2, TP212.1, U225.7
VCO1_SQR: C272.2, J201.7, R317.1, TP218.1, U226.7
VCO1_SQR_SHAPE: J201.5, R316.1, U227.6 (-)
VCO1_SYNC: J202.15, R323.1, U205.5 (+)
VCO1_TRI: C271.1, J201.1, R310.1, TP214.1, U227.1
VCO2_AUDIO: J202.3, RV205.3
VCO2_CV: C207.1, J202.5, R201.2, R202.1, R203.1, R318.2, U201.2 (-)
VCO2_FM: J202.7, R205.1
VCO2_SAW: D203.2 (A), J201.11, R255.1, R258.2, TP211.1, U209.7
VCO2_SQR: C236.2, J201.15, R263.1, TP217.1, U210.7
VCO2_SQR_SHAPE: J201.13, R262.1, U211.6 (-)
VCO2_SYNC: J202.9, R322.1, U202.5 (+)
VCO2_TRI: C235.1, J201.9, R256.1, TP213.1, U211.1

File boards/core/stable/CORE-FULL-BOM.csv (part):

"Reference","Value","Datasheet","Footprint","Qty","DNP","LCSC","Part No.","Part URL","Vendor"
"C201,C202,C203,C204,C205,C206,C211,C212,C213,C214,C215,C216,C221,C222,C223,C224,C229,C230,C231,C232,C233,C234,C237,C238,C239,C242,C243,C244,C245,C246,C247,C249,C250,C253,C254,C257,C258,C259,C262,C263,C265,C266,C267,C268,C269,C270,C278,C279","100n","~","Capacitor_SMD:C_0603_1608Metric","48","","C14663","","","JLCPCB"
"C208,C218,C276","100p","~","Capacitor_SMD:C_0603_1608Metric","3","","C14858","","","JLCPCB"
"C210,C220","22p","~","Capacitor_SMD:C_0603_1608Metric","2","","C1653","","","JLCPCB"
"C225,C226,C227,C275","22uF","~","Capacitor_SMD:CP_Elec_6.3x5.4","4","","C2836438","","","JLCPCB"
"C236,C272","33p","~","Capacitor_SMD:C_0603_1608Metric","2","","C1663","","","JLCPCB"
"C240","10n","~","Capacitor_SMD:C_0603_1608Metric","1","","C57112","","","JLCPCB"
"C241","10u","~","Capacitor_THT:CP_Radial_D6.3mm_P2.50mm","1","","","598-106RSS050M ","https://mou.sr/3VxA0hV","Mouser"
"C248","1u (foil or electrolite)","~","Capacitor_THT:C_Rect_L7.2mm_W5.5mm_P5.00mm_FKS2_FKP2_MKS2_MKP2","1","","","80-R82EC4100Z370K ","https://mou.sr/3ZROEn2","Mouser"
"C251,C255","22n-47n (foil)","~","Capacitor_THT:C_Rect_L7.0mm_W2.5mm_P5.00mm","2","","","80-R82EC1330AA50K ","https://mou.sr/3BhmOHr","Mouser"
"C252,C256,C280,C281","47u","~","Capacitor_SMD:CP_Elec_6.3x5.4","4","","C3344","","","JLCPCB"
"C260,C261","100u","~","Capacitor_SMD:CP_Elec_6.3x7.7","2","","C2836437","","","JLCPCB"
"C273,C274,C282,C283,C284,C285","47p","~","Capacitor_SMD:C_0603_1608Metric","6","","C1671","","","JLCPCB"
"C277","1u","~","Capacitor_SMD:C_0603_1608Metric_Pad1.08x0.95mm_HandSolder","1","","C15849","","","JLCPCB"
"D203,D204,D207,D212,D213,D216,D217","1N4148","~","Diode_SMD:D_SOD-123","7","","C81598","","","JLCPCB"
"J201,J202,J203,J204","Conn_02x08_Counter_Clockwise","~","Connector_PinHeader_2.54mm:PinHeader_2x08_P2.54mm_Vertical","4","","","737-RS2-16-G ","https://mou.sr/3OWyRwS","Mouser"
"J214","Conn_02x04_Counter_Clockwise","~","Connector_PinHeader_2.54mm:PinHeader_2x04_P2.54mm_Vertical","1","","","737-RS2-08-G ","https://mou.sr/41qYCwK","Mouser"
"J_POWER201","Conn_02x05_Odd_Even","~","Connector_PinHeader_2.54mm:PinHeader_2x05_P2.54mm_Vertical","1","","","737-RS2-10-G ","https://mou.sr/3ZuUKrQ","Mouser"
"Q201,Q204","2N3906","https://www.tme.eu/Document/1d69ece8147fa5a64114d103f531c790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","Package_TO_SOT_THT:TO-92L_Inline_Wide","2","","","512-2N3906BU ","https://mou.sr/3ZrOXn8","Mouser"
"Q202,Q205","BC847BS","https://www.tme.eu/Document/82748fbc26f250e671ae2786c3be5a04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","Package_TO_SOT_SMD:SOT-363_SC-70-6_Handsoldering","2","","C5380687","","","JLCPCB"
"Q203,Q206","MMBFJ111","https://www.tme.eu/Document/2ab8d7a6d6d8a209f9d7deeb52763e9f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","PCM_Package_TO_SOT_SMD_AKL:SOT-23_Handsoldering","2","","","512-MMBFJ111 ","https://mou.sr/3Us0WP4","Mouser"
"Q207","BC847BS","https://www.tme.eu/Document/82748fbc26f250e671ae2786c3be5a04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","Package_TO_SOT_SMD:SOT-363_SC-70-6","1","","C5380687","","","JLCPCB"
"Q208,Q209,Q210","BC548C","https://www.onsemi.com/pub/Collateral/BC550-D.pdf","Package_TO_SOT_THT:TO-92L_Inline_Wide","3","","","637-BC548C ","https://mou.sr/4fhkHkJ","Mouser"
"Q212,Q213,Q214","MMBT5551","https://datasheet.lcsc.com/lcsc/2304140030_Jiangsu-Changjing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","Package_TO_SOT_SMD:SOT-23","3","","C2145","","","JLCPCB"
"R201,R213,R216,R228,R232,R235,R237,R242,R243,R244,R246,R247,R250,R252,R253,R254,R255,R262,R263,R264,R278,R279,R280,R281,R282,R283,R284,R285,R286,R287,R301,R304,R306,R307,R308,R309,R316,R317,R318,R319,R326,R327,R328,R329,R335,R336,R337,R338,R339,R340","100k","~","Resistor_SMD:R_0603_1608Metric","50","","C25803","","","JLCPCB"
"R202,R212,R217,R227","150k","~","Resistor_SMD:R_0603_1608Metric","4","","C22807","","","JLCPCB"
"R203,R218","91k","~","Shmoergh_Custom_Footprints:R_Axial_DIN0207_L6.3mm_D2.5mm_P7.62mm_Horizontal","2","","","603-MFR50SFTE52-91K ","https://mou.sr/3Vwa9XS","Mouser"
"R204,R219","6.2k (50ppm)","~","Shmoergh_Custom_Footprints:R_Axial_DIN0207_L6.3mm_D2.5mm_P7.62mm_Horizontal","2","","","603-MFR50SFTE52-6K2 ","https://mou.sr/3OL65PP","Mouser"
"R205,R208,R220,R223,R322,R323","1M","~","Resistor_SMD:R_0603_1608Metric","6","","C22935","","","JLCPCB"
"R206,R221","4R22 (50ppm)","~","Shmoergh_Custom_Footprints:R_Axial_DIN0207_L6.3mm_D2.5mm_P7.62mm_Horizontal","2","","","603-MFR50SFTE52-4R22 ","https://mou.sr/49tYeQ0","Mouser"
"R207,R209,R222,R224","1.5k","~","Resistor_SMD:R_0603_1608Metric","4","","C22843","","","JLCPCB"
"R210,R225","510","~","Resistor_SMD:R_0603_1608Metric","2","","C23193","","","JLCPCB"
"R211,R226","22k","~","Resistor_SMD:R_0603_1608Metric","2","","C31850","","","JLCPCB"
"R214,R229","330k","~","Resistor_SMD:R_0603_1608Metric","2","","C23137","","","JLCPCB"
"R215,R230,R258,R297,R312","2.2k","~","Resistor_SMD:R_0603_1608Metric","5","","C4190","","","JLCPCB"
"R231","4.7k","~","Resistor_SMD:R_0603_1608Metric","1","","C23162","","","JLCPCB"
"R233","220","~","Resistor_SMD:R_0603_1608Metric","1","","C22962","","","JLCPCB"
"R234,R245","33k","~","Resistor_SMD:R_0603_1608Metric","2","","C4216","","","JLCPCB"
"R236,R238,R239,R266,R288,R289,R324,R325","10k","~","Resistor_SMD:R_0603_1608Metric","8","","C25804","","","JLCPCB"
"R240,R241,R296","470k","~","Resistor_SMD:R_0603_1608Metric","3","","C23178","","","JLCPCB"
"R248,R249,R302,R303","15k","~","Resistor_SMD:R_0603_1608Metric","4","","C22809","","","JLCPCB"
"R251,R305","27k","~","Resistor_SMD:R_0603_1608Metric","2","","C22967","","","JLCPCB"
"R256,R259,R310,R313,R320","220k","~","Resistor_SMD:R_0603_1608Metric","5","","C22961","","","JLCPCB"
"R257,R267,R290,R291,R292,R293,R311,R321,R330,R331,R332,R333,R334","47k","~","Resistor_SMD:R_0603_1608Metric","13","","C25819","","","JLCPCB"
"R260,R314","2.2M","~","Resistor_SMD:R_0603_1608Metric","2","","C22938","","","JLCPCB"
"R261,R300,R315","240k","~","Resistor_SMD:R_0603_1608Metric","3","","-- mixed values --","","","JLCPCB"
"R265","75k","~","Resistor_SMD:R_0603_1608Metric","1","","C23242","","","JLCPCB"
"R268","470","~","Shmoergh_Custom_Footprints:R_Axial_DIN0207_L6.3mm_D2.5mm_P7.62mm_Horizontal","1","","","303-CFR0W4J0471B00 ","https://mou.sr/49DiyPd","Mouser"
"R269,R272,R277,R294,R295","1k","~","Resistor_SMD:R_0603_1608Metric","5","","C21190","","","JLCPCB"
"R270","100k","~","Resistor_SMD:R_0603_1608Metric_Pad0.98x0.95mm_HandSolder","1","","C25803","","","JLCPCB"
"R271","150","~","Resistor_SMD:R_0603_1608Metric","1","","C22808","","","JLCPCB"
"R273,R274","100","~","Resistor_SMD:R_0603_1608Metric","2","","C22775","","","JLCPCB"
"R298","3.3M","~","Resistor_SMD:R_0603_1608Metric","1","","C141659","","","JLCPCB"
"RV201,RV202,RV203,RV204,RV205,RV_HEADPHONE_LIM201","100k","~","Potentiometer_THT:Potentiometer_ACP_CA6-H2,5_Horizontal","6","","","531-PT6KH104A1010PM ","https://mou.sr/49zQlIS","Mouser"
"RV_ADSR_MAX_VOLTAGE201,RV_TRI_BIAS201,RV_TRI_BIAS202","100k","~","Potentiometer_THT:Potentiometer_Bourns_3006P_Horizontal","3","","","652-3006P-1-104-LF ","https://mou.sr/4ff5W1E","Mouser"
"RV_LINE_OUT_LVL201","10k","~","Potentiometer_THT:Potentiometer_ACP_CA6-H2,5_Horizontal","1","","","531-PT6KH-10K ","https://mou.sr/4gcYhlU","Mouser"
"RV_SAW_BIAS201,RV_SAW_BIAS202","10k","~","Potentiometer_THT:Potentiometer_Bourns_3006P_Horizontal","2","","","652-3006P-1-103-LF ","https://mou.sr/41xh2vW","Mouser"
"R_WIDTH201,R_WIDTH202","20k","~","Potentiometer_THT:Potentiometer_Bourns_3006P_Horizontal","2","","","652-3006P-7-203-LF ","https://mou.sr/41re1x3","Mouser"
"TH201,TH202","PTS120601B100RP100","~","Resistor_SMD:R_1206_3216Metric_Pad1.30x1.75mm_HandSolder","2","","","594-PTS120601B100RP ","https://mou.sr/4g7SsGi","Mouser"
"U201,U202,U204,U205,U207,U208,U209,U210,U211,U214,U217,U218,U219,U220,U221,U222,U223,U225,U226,U227","TL072","http://www.ti.com/lit/ds/symlink/tl071.pdf","Package_SO:SOIC-8_3.9x4.9mm_P1.27mm","20","","C6961","","","JLCPCB"
"U203,U206","LM311","https://www.st.com/resource/en/datasheet/lm311.pdf","Package_SO:SOIC-8_3.9x4.9mm_P1.27mm","2","","C12597","","","JLCPCB"
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
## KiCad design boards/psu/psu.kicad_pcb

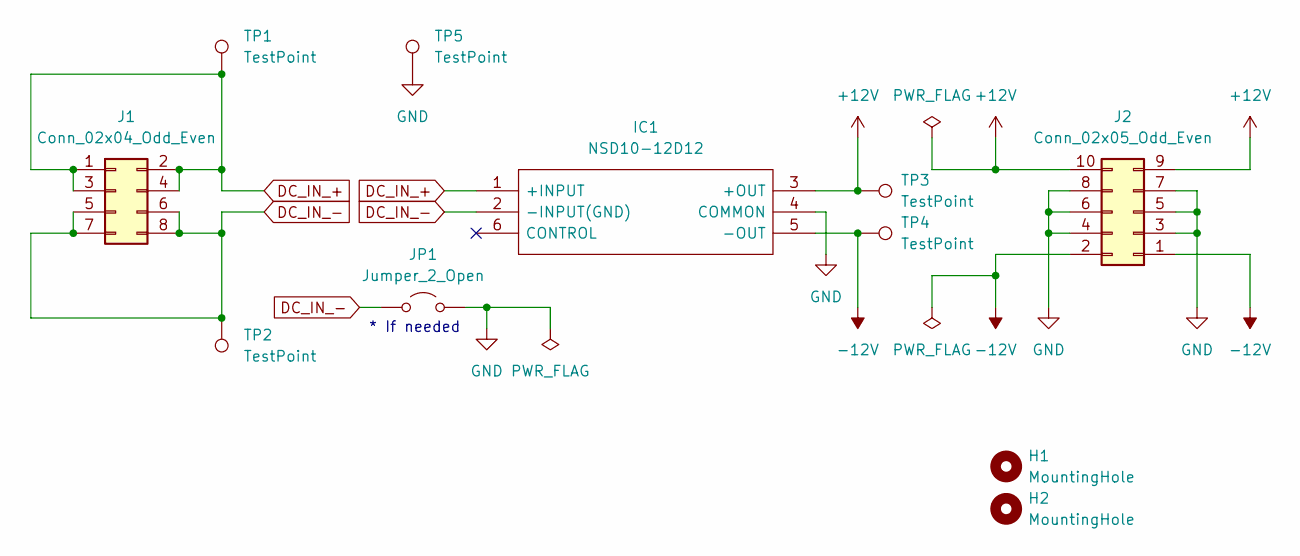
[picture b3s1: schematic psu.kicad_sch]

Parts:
H1, H2: MountingHole; MountingHole_3mm_Pad; Part No. N/A
IC1: NSD10-12D12; NSD1012D5; Manufacturer_Part_Number NSD10-12D12; Mouser Part Number 709-NSD10-12D5
J1: Conn_02x04_Odd_Even; PinSocket_2x04_P2.54mm_Vertical; Part No. 737-RS2-08-G
J2: Conn_02x05_Odd_Even; PinSocket_2x05_P2.54mm_Vertical; Part No. 737-RS2-10-G
JP1: Jumper_2_Open; SolderJumper-2_P1.3mm_Open_Pad1.0x1.5mm; Part No. N/A
TP1, TP2, TP3, TP4, TP5: TestPoint; TestPoint_THTPad_2.0x2.0mm_Drill1.0mm; Part No. N/A

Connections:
+12V: IC1.3 (+OUT), J2.9, J2.10, TP3.1
-12V: IC1.5 (-OUT), J2.1, J2.2, TP4.1
DC_IN_+: IC1.1 (+INPUT), J1.1, J1.2, J1.3, J1.4, TP1.1
DC_IN_-: IC1.2 (-INPUT(GND)), J1.5, J1.6, J1.7, J1.8, JP1.1 (A), TP2.1
GND: IC1.4 (COMMON), J2.3, J2.4, J2.5, J2.6, J2.7, J2.8, JP1.2 (B), TP5.1

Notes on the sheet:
* If needed
